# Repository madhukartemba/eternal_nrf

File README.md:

# eternal_nrf
A solar powered nRF based BLE contact sensor.

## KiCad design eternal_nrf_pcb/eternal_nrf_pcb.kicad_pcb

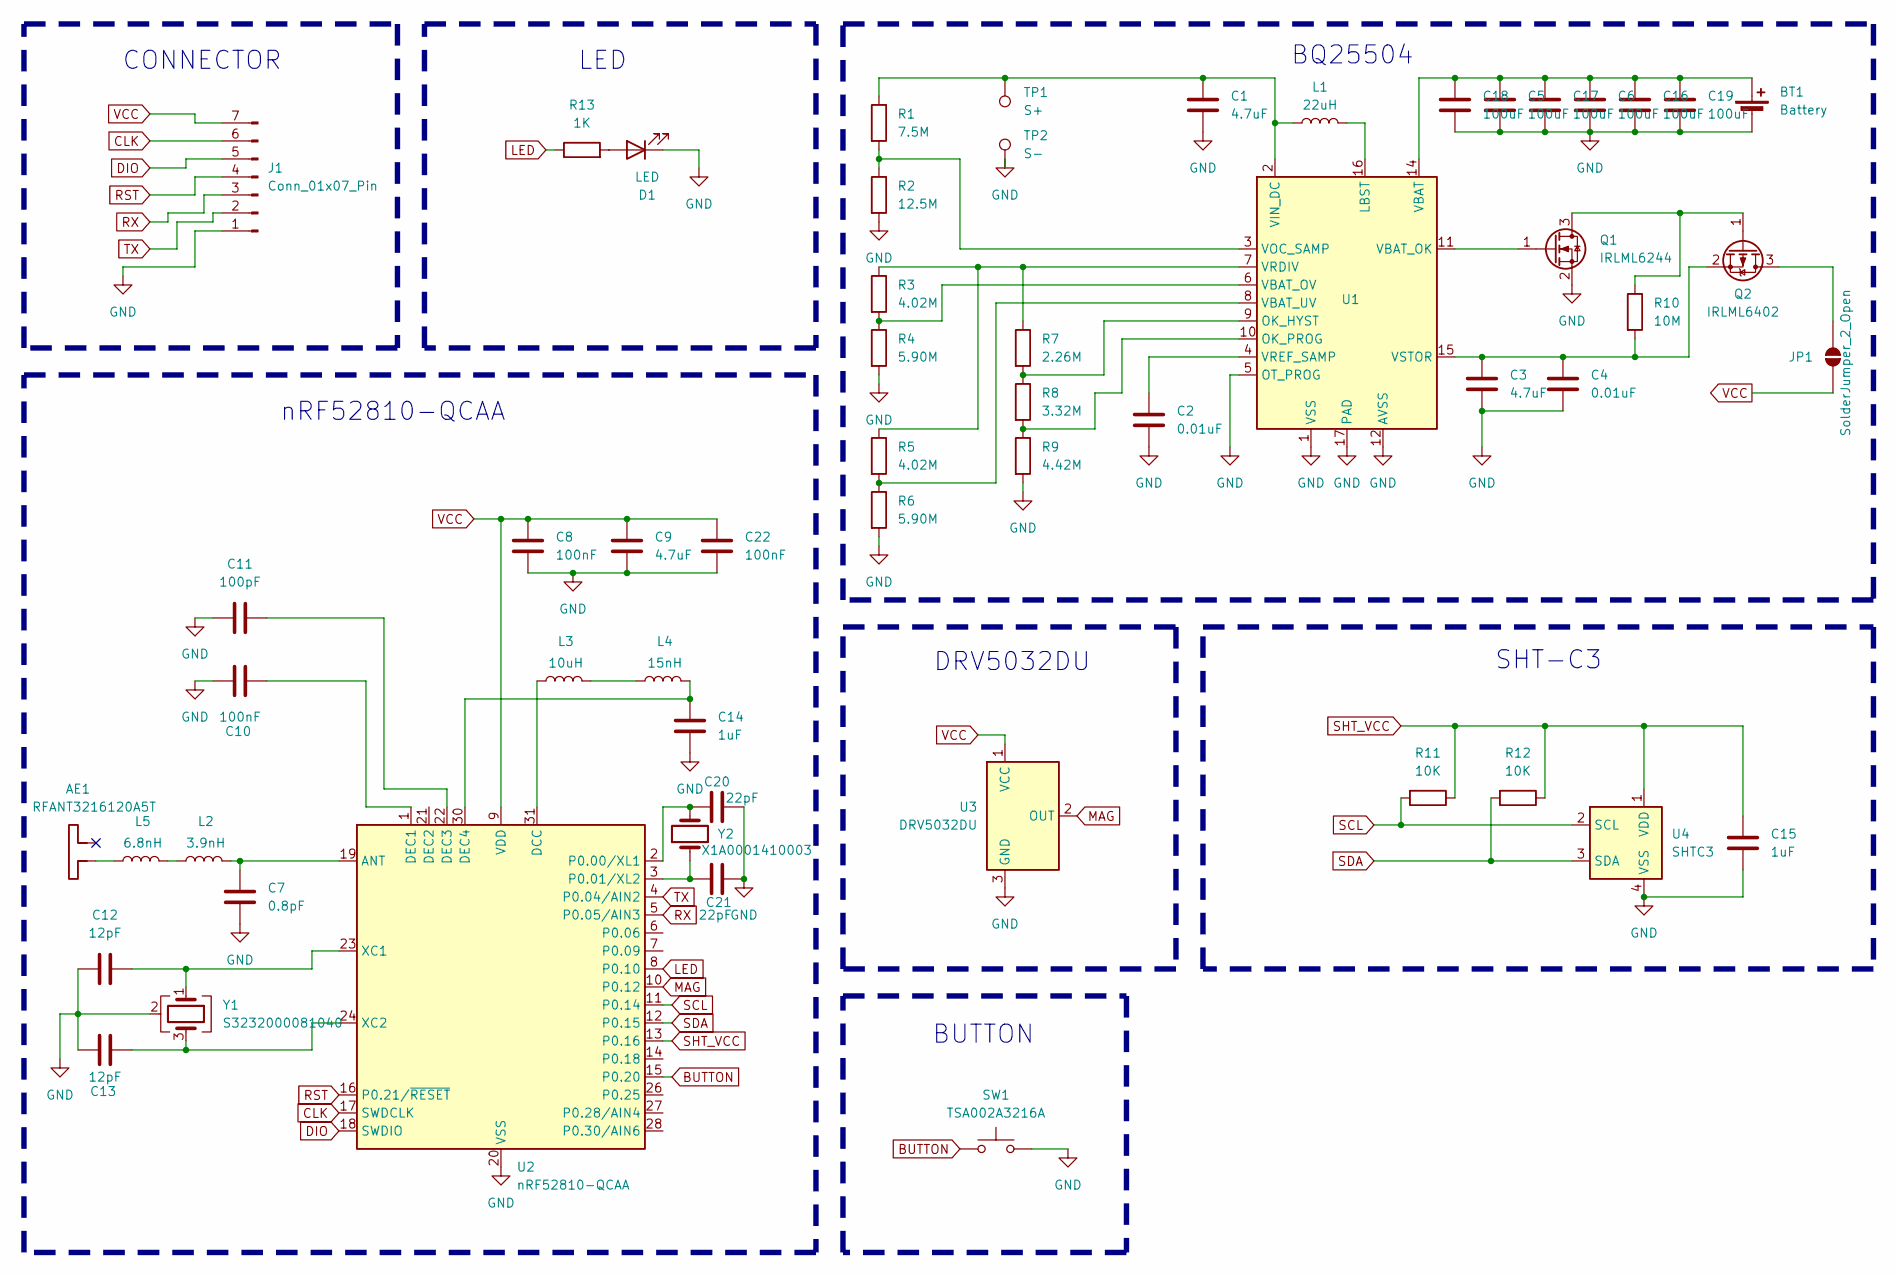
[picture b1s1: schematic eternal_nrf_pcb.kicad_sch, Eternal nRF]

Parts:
AE1: RFANT3216120A5T; Johanson_2450AT18x100
BT1: Battery; BatteryHolder_Seiko_MS621F
C1, C3: 4.7uF; C_0805_2012Metric
C2, C4: 0.01uF; C_0603_1608Metric
C5, C6, C16, C17, C18, C19: 100uF; C_1210_3225Metric
C7: 0.8pF; C_0402_1005Metric_Pad0.74x0.62mm_HandSolder
C8, C10, C22: 100nF; C_0402_1005Metric_Pad0.74x0.62mm_HandSolder
C9: 4.7uF; C_0603_1608Metric_Pad1.08x0.95mm_HandSolder
C11: 100pF; C_0402_1005Metric_Pad0.74x0.62mm_HandSolder
C12, C13: 12pF; C_0402_1005Metric_Pad0.74x0.62mm_HandSolder
C14, C15: 1uF; C_0402_1005Metric_Pad0.74x0.62mm_HandSolder
C20, C21: 22pF; C_0402_1005Metric_Pad0.74x0.62mm_HandSolder
D1: LED; LED_0603_1608Metric
J1: Conn_01x07_Pin; PinHeader_1x07_P2.54mm_Vertical
JP1: SolderJumper_2_Open; SolderJumper-2_P1.3mm_Open_TrianglePad1.0x1.5mm
L1: 22uH; L_Sunlord_SWPA4030S
L2: 3.9nH; L_0402_1005Metric_Pad0.77x0.64mm_HandSolder
L3: 10uH; L_0603_1608Metric_Pad1.05x0.95mm_HandSolder
L4: 15nH; L_0402_1005Metric_Pad0.77x0.64mm_HandSolder
L5: 6.8nH; L_0402_1005Metric_Pad0.77x0.64mm_HandSolder
Q1: IRLML6244; SOT-23
Q2: IRLML6402; SOT-23
R1: 7.5M; R_0603_1608Metric_Pad0.98x0.95mm_HandSolder
R2: 12.5M; R_0603_1608Metric_Pad0.98x0.95mm_HandSolder
R3, R5: 4.02M; R_0603_1608Metric_Pad0.98x0.95mm_HandSolder
R4, R6: 5.90M; R_0603_1608Metric_Pad0.98x0.95mm_HandSolder
R7: 2.26M; R_0603_1608Metric_Pad0.98x0.95mm_HandSolder
R8: 3.32M; R_0603_1608Metric_Pad0.98x0.95mm_HandSolder
R9: 4.42M; R_0603_1608Metric_Pad0.98x0.95mm_HandSolder
R10: 10M; R_0603_1608Metric_Pad0.98x0.95mm_HandSolder
R11, R12: 10K; R_0402_1005Metric_Pad0.72x0.64mm_HandSolder
R13: 1K; R_0402_1005Metric_Pad0.72x0.64mm_HandSolder
SW1: TSA002A3216A; TST-A002_0.6MM_BOSS
TP1: S+; TestPoint_Pad_D2.0mm
TP2: S-; TestPoint_Pad_D2.0mm
U1: BQ25504; VQFN-16-1EP_3x3mm_P0.5mm_EP1.68x1.68mm
U2: nRF52810-QCAA; QFN-32-1EP_5x5mm_P0.5mm_EP3.6x3.6mm
U3: DRV5032DU; SOT-23
U4: SHTC3; Sensirion_DFN-4-1EP_2x2mm_P1mm_EP0.7x1.6mm
Y1: S3232000081040; Crystal_SMD_3225-4Pin_3.2x2.5mm
Y2: X1A0001410003; Crystal_SMD_3215-2Pin_3.2x1.5mm

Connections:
BUTTON: SW1.1, U2.15 (P0.20)
CLK: J1.6, U2.17 (SWDCLK)
DIO: J1.5, U2.18 (SWDIO)
GND: BT1.2 (-), C1.2, C2.2, C3.2, C4.2, C5.2, C6.2, C7.2, C8.2, C9.2, C10.1, C11.1, C12.1, C13.1, C14.2, C15.2, C16.2, C17.2, C18.2, C19.2, C20.1, C21.2, C22.2, D1.1 (K), J1.1, Q1.2 (S), R2.2, R4.2, R6.2, R9.2, SW1.2, TP2.1 (1_1), U1.1 (VSS), U1.5 (OT_PROG), U1.12 (AVSS), U1.13 (VSS), U1.17 (PAD), U2.20 (VSS), U2.29 (VSS), U2.33 (VSS), U3.3 (GND), U4.4 (VSS), Y1.2 (G), Y1.4 (G)
LED: R13.1, U2.8 (P0.10)
MAG: U2.10 (P0.12), U3.2 (OUT)
unnamed: AE1.1, L5.1
unnamed: BT1.1 (+), C5.1, C6.1, C16.1, C17.1, C18.1, C19.1, U1.14 (VBAT)
unnamed: D1.2 (A), R13.2
unnamed: JP1.2 (B), Q2.3 (D)
unnamed: L2.1, L5.2
unnamed: L3.2, L4.1
unnamed: Q1.3 (D), Q2.1 (G), R10.1
unnamed: Q1.1 (G), U1.11 (VBAT_OK)
unnamed: C3.1, C4.1, Q2.2 (S), R10.2, U1.15 (VSTOR)
unnamed: L1.2, U1.16 (LBST)
unnamed: R7.2, R8.1, U1.9 (OK_HYST)
unnamed: R8.2, R9.1, U1.10 (OK_PROG)
unnamed: R3.2, R4.1, U1.6 (VBAT_OV)
unnamed: R5.2, R6.1, U1.8 (VBAT_UV)
unnamed: C1.1, L1.1, R1.1, TP1.1 (1_1), U1.2 (VIN_DC)
unnamed: R1.2, R2.1, U1.3 (VOC_SAMP)
unnamed: R3.1, R5.1, R7.1, U1.7 (VRDIV)
unnamed: C2.1, U1.4 (VREF_SAMP)
unnamed: C7.1, L2.2, U2.19 (ANT)
unnamed: L3.1, U2.31 (DCC)
unnamed: C10.2, U2.1 (DEC1)
unnamed: C11.2, U2.22 (DEC3)
unnamed: C14.1, L4.2, U2.30 (DEC4)
unnamed: C21.1, U2.2 (P0.00/XL1), Y2.2
unnamed: C20.2, U2.3 (P0.01/XL2), Y2.1
unnamed: C12.2, U2.23 (XC1), Y1.1
unnamed: C13.2, U2.24 (XC2), Y1.3
RST: J1.4, U2.16 (P0.21/~RESET)
RX: J1.3, U2.5 (P0.05/AIN3)
SCL: R11.2, U2.11 (P0.14), U4.2 (SCL)
SDA: R12.2, U2.12 (P0.15), U4.3 (SDA)
SHT_VCC: C15.1, R11.1, R12.1, U2.13 (P0.16), U4.1 (VDD)
TX: J1.2, U2.4 (P0.04/AIN2)
VCC: C8.1, C9.1, C22.1, J1.7, JP1.1 (A), U2.9 (VDD), U2.25 (VDD), U2.32 (VDD), U3.1 (VCC)

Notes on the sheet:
BQ25504
BUTTON
nRF52810-QCAA
DRV5032DU
CONNECTOR
SHT-C3
LED

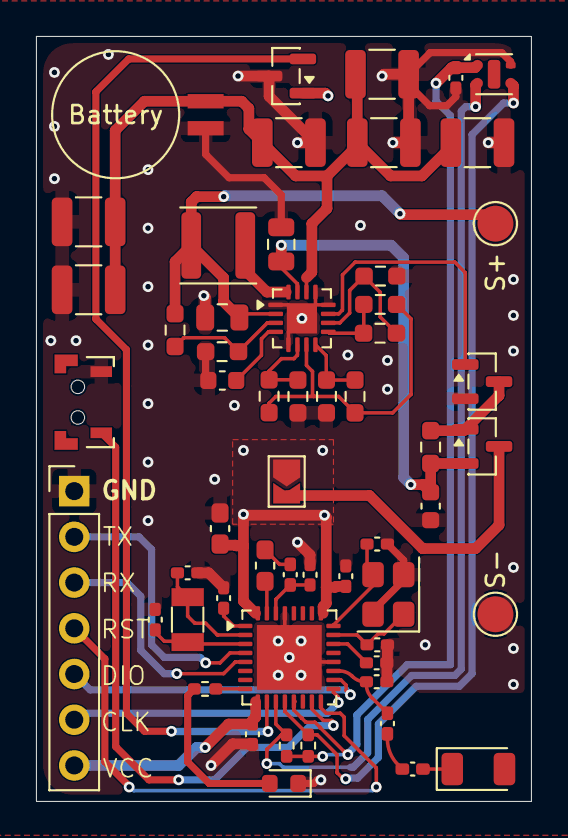
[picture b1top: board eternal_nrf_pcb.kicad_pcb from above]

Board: 4 copper layers, 27.5 x 42.5 mm, 56 parts (0 on the bottom side), 40 nets.

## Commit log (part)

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2026-05-04 add resistor values
2026-05-05 add nrf barebones schema
2026-05-05 add footprints
2026-05-05 add button and led
2026-05-05 add footprint
2026-05-06 place parts
2026-05-08 almost final layout
2026-05-08 somewhat complete wiring
2026-05-08 almost complete design, touch ups are pending
2026-05-08 change fonts
2026-05-08 final pcb (rev 1 :))
2026-05-08 update sheet info
2026-05-08 add pdf
2026-05-10 complete board
2026-05-10 increase trace width
2026-05-10 add production file
2026-05-10 fix bugs
2026-05-10 add backups file
2026-05-10 final production file
2026-05-19 add missing route :(
2026-05-19 add bq25504 schema
2026-05-28 add src code
2026-06-01 add battery less version
2026-06-01 update battery less code
2026-06-01 flash led breifly
